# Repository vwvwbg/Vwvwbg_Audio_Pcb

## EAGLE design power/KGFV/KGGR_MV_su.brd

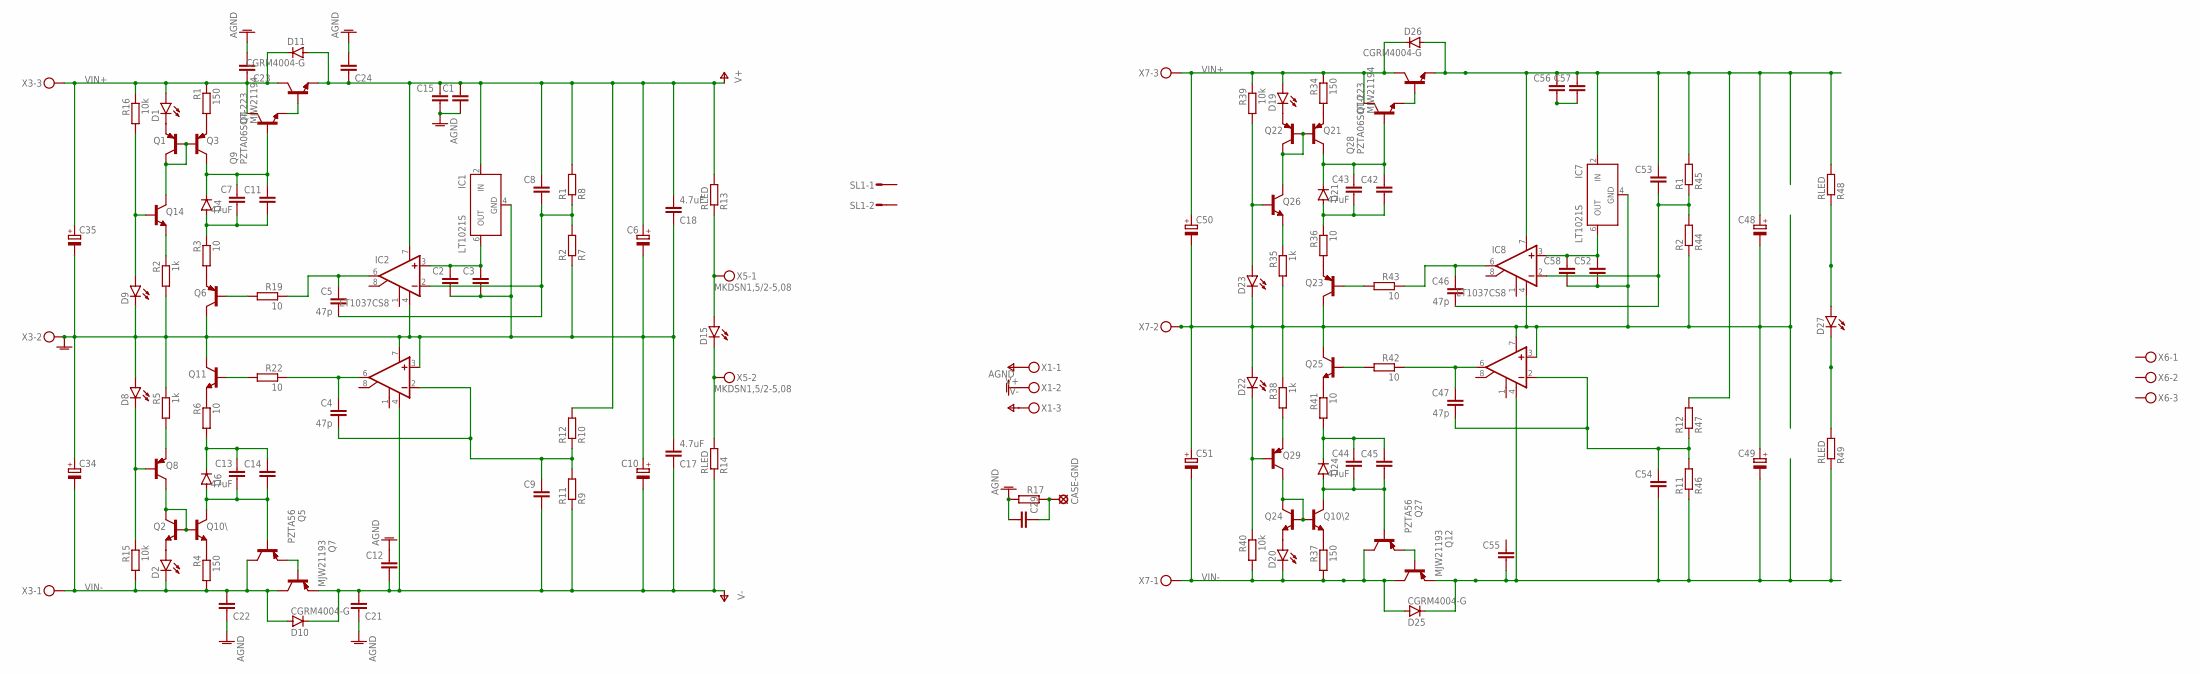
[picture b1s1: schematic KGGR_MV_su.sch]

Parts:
C1, C2, C3, C8, C9, C11, C12, C14, C15, C42, C45, C52, C53, C54, C55, C56, C57, C58: C-EUC0805; C0805
C4, C5, C46, C47: 47p; C0805
C6, C10, C48, C49: CPOL-EUE5-13; E5-13
C7, C13, C43, C44: 47uF; C1206
C17, C18: 4.7uF; C050-075X075
C21, C24: C-EU050-035X075; C050-035X075
C22, C23: C-EU050-075X075; C050-075X075
C29: C-EU102_152-062X184; C102_152-062X184
C34, C35, C50, C51: CPOL-EUE7.5-18; E7,5-18
CASE-GND: SE14
D1, D2, D8, D9, D15, D19, D20, D22, D23, D27: LEDSML0805; SML0805
D4, D21: TZMC10; SOD80C
D6, D24: TZAMC10; SOD80C
D10, D11, D25, D26: CGRM4004-G; SOD-123_MINI-SMA
IC1, IC7: LT1021S; SOIC8
IC2, IC3: LT1037CS8; SOIC8
IC8, IC9: LT1037CS8; SO08
Q1, Q3, Q6, Q8, Q21, Q22, Q23, Q29: TRANSISTOR_BC857C-PNP-SOT23-BEC; TRANSISTOR_SOT23-BEC
Q2, Q10\, Q10\2, Q11, Q14, Q24, Q25, Q26: TRANSISTOR_BC847CLT1-NPN-SOT23-BEC; TRANSISTOR_SOT23-BEC
Q4, Q10: MJW21194; TO-264
Q5, Q27: PZTA56; SOT223
Q7, Q12: MJW21193; TO-264
Q9, Q28: PZTA06SOT-223; SOT223
R1, R4, R34, R37: 150; MINI_MELF-0204W
R2, R5, R35, R38: 1k; MINI_MELF-0204W
R3, R6, R19, R22, R36, R41, R42, R43: 10; MINI_MELF-0204W
R7, R44: R2; MINI_MELF-0204W
R8, R45: R1; MINI_MELF-0204W
R9, R46: R11; MINI_MELF-0204W
R10, R47: R12; MINI_MELF-0204W
R13, R14, R48, R49: RLED; MINI_MELF-0204W
R15, R16, R39, R40: 10k; MINI_MELF-0204W
R17: R-EU_0617/22; 0617/22
SL1: M02S; 02P
X1, X3, X6, X7: MKDSN1,5/3-5,08
X5: MKDSN1,5/2-5,08

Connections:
AGND: C1.2, C2.2, C3.2, C6.-, C10.+, C12.1, C15.2, C17.2, C18.1, C21.1, C22.1, C23.2, C24.2, C29.2, C29.3 (2), C34.+, C35.-, C48.-, C49.+, C50.-, C51.+, C52.2, C55.1, C56.2, C57.2, C58.2, D8.A, D9.C, D22.A, D23.C, IC1.4 (GND), IC2.4 (V-), IC3.3 (+IN), IC3.7 (V+), IC7.4 (GND), IC8.4 (V-), IC9.3 (+IN), IC9.7 (V+), Q6.C, Q11.C, Q23.C, Q25.C, R2.2, R5.1, R7.1, R17.2, R35.2, R38.1, R44.1, X1.2, X3.2, X6.2, X7.2
unnamed: Q1.B, Q1.C, Q3.B, Q14.C
unnamed: D1.C, Q1.E
unnamed: Q3.E, R1.2
unnamed: C7.1, C11.1, D4.C, Q3.C, Q9.1 (B)
unnamed: C7.2, C11.2, D4.A, R3.1
unnamed: Q6.E, R3.2
unnamed: Q14.E, R2.1
unnamed: D9.A, Q14.B, R16.2
unnamed: C4.1, IC3.6 (OUT), R22.1
unnamed: Q8.E, R5.2
unnamed: D8.C, Q8.B, R15.1
unnamed: Q11.E, R6.1
unnamed: C13.1, C14.1, D6.C, R6.2
unnamed: C13.2, C14.2, D6.A, Q5.1 (B), Q10\.C
unnamed: Q2.B, Q2.C, Q8.C, Q10\.B
unnamed: Q5.3 (E), Q7.B
unnamed: Q10\.E, R4.1
unnamed: D2.A, Q2.E
unnamed: Q4.B, Q9.3 (E)
unnamed: C4.2, C9.1, IC3.2 (-IN), R9.2, R10.1
unnamed: C5.1, IC2.6 (OUT), R19.1
unnamed: Q11.B, R22.2
unnamed: Q6.B, R19.2
unnamed: C5.2, C8.2, IC2.2 (-IN), R7.2, R8.1
unnamed: C2.1, C3.1, IC1.6 (OUT), IC2.3 (+IN)
unnamed: D15.C, R14.2, X5.2
unnamed: D15.A, R13.1, X5.1
unnamed: C29.1, CASE-GND.MP, R17.1
unnamed: Q21.B, Q22.B, Q22.C, Q26.C
unnamed: D19.C, Q22.E
unnamed: Q21.E, R34.2
unnamed: C42.1, C43.1, D21.C, Q21.C, Q28.1 (B)
unnamed: C42.2, C43.2, D21.A, R36.1
unnamed: Q23.E, R36.2
unnamed: Q26.E, R35.1
unnamed: D23.A, Q26.B, R39.2
unnamed: Q29.E, R38.2
unnamed: D22.C, Q29.B, R40.1
unnamed: Q25.E, R41.1
unnamed: C44.1, C45.1, D24.C, R41.2
unnamed: C44.2, C45.2, D24.A, Q10\2.C, Q27.1 (B)
unnamed: Q10\2.B, Q24.B, Q24.C, Q29.C
unnamed: Q10\2.E, R37.1
unnamed: D20.A, Q24.E
unnamed: Q12.B, Q27.3 (E)
unnamed: Q10.B, Q28.3 (E)
unnamed: Q25.B, R42.2
unnamed: Q23.B, R43.2
unnamed: C46.2, C53.2, IC8.2 (-IN), R44.2, R45.1
unnamed: D27.C, R49.2
unnamed: D27.A, R48.1
unnamed: C47.1, IC9.6 (OUT), R42.1
unnamed: C47.2, C54.1, IC9.2 (-IN), R46.2, R47.1
unnamed: C52.1, C58.1, IC7.6 (OUT), IC8.3 (+IN)
unnamed: C46.1, IC8.6 (OUT), R43.1
V+: C1.1, C6.+, C8.1, C15.1, C18.2, C24.1, D11.A, IC1.2 (IN), IC2.7 (V+), Q4.E, R8.2, R10.2, R13.2, X1.1
V+2: C48.+, C53.1, C56.1, C57.1, D26.A, IC7.2 (IN), IC8.7 (V+), Q10.E, R45.2, R47.2, R48.2, X6.1
V-: C9.2, C10.-, C12.2, C17.1, C21.2, D10.C, IC3.4 (V-), Q7.E, R9.1, R14.1, X1.3
V-2: C49.-, C54.2, C55.2, D25.C, IC9.4 (V-), Q12.E, R46.1, R49.1, X6.3
VIN+: C23.1, C35.+, C50.+, D1.A, D11.C, D19.A, D26.C, Q4.C, Q9.2 (C), Q9.4 (C), Q10.C, Q28.2 (C), Q28.4 (C), R1.1, R16.1, R34.1, R39.1, X3.3, X7.3
VIN-: C22.2, C34.-, C51.-, D2.C, D10.A, D20.C, D25.A, Q5.2 (C), Q5.4 (C), Q7.C, Q12.C, Q27.2 (C), Q27.4 (C), R4.2, R15.2, R37.2, R40.2, X3.1, X7.1

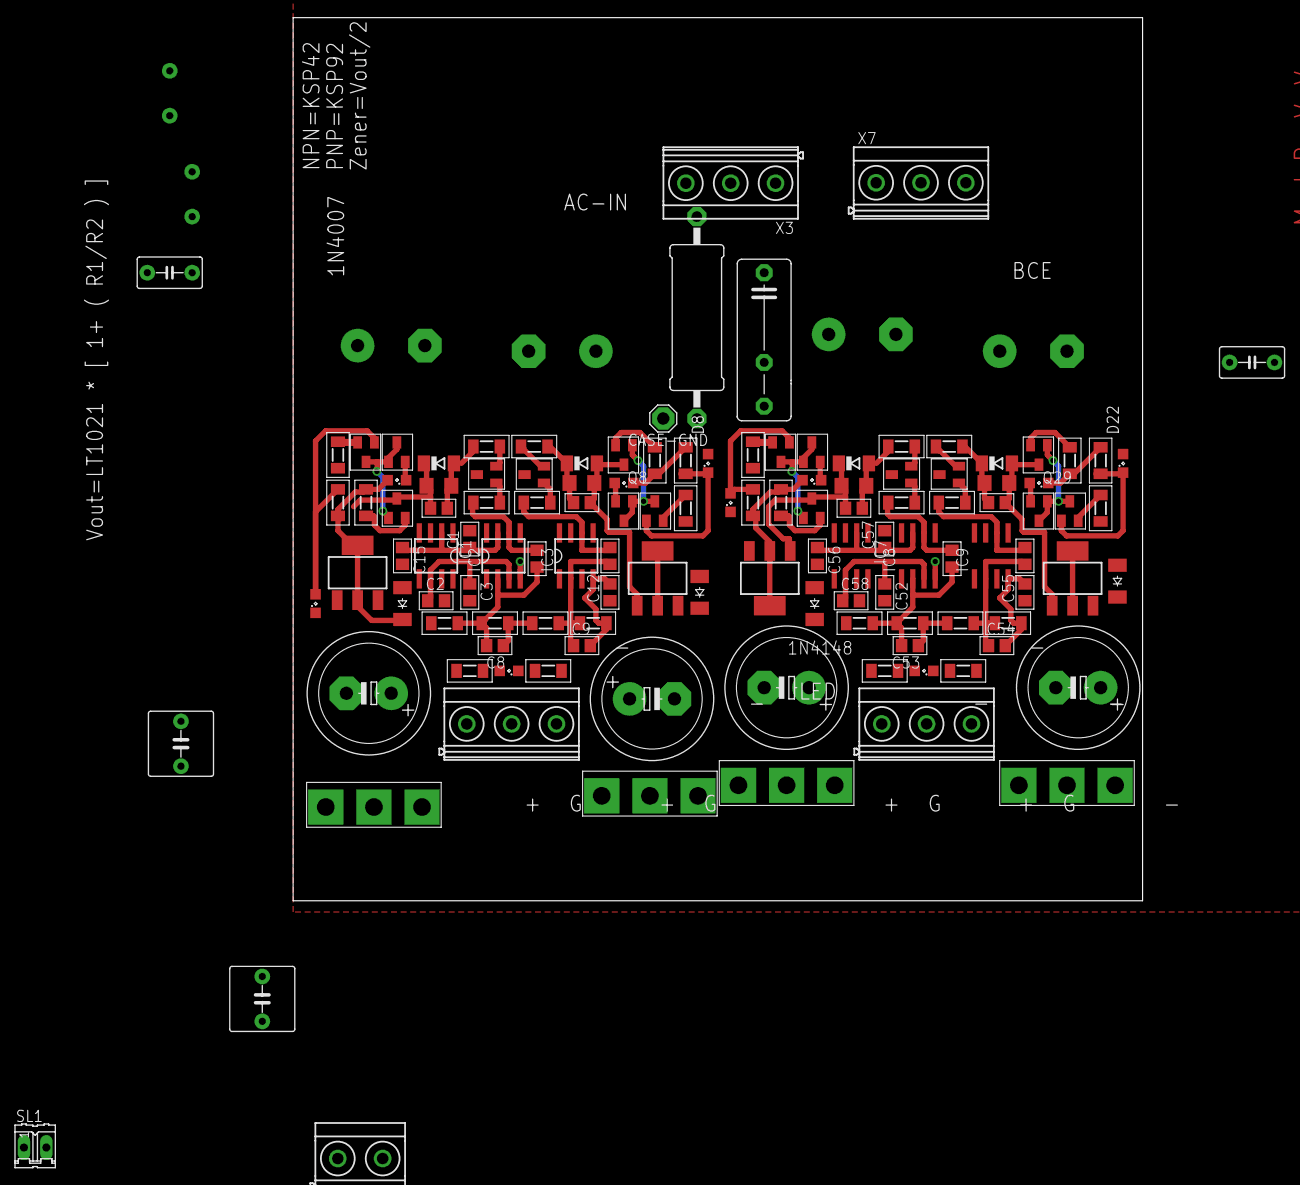
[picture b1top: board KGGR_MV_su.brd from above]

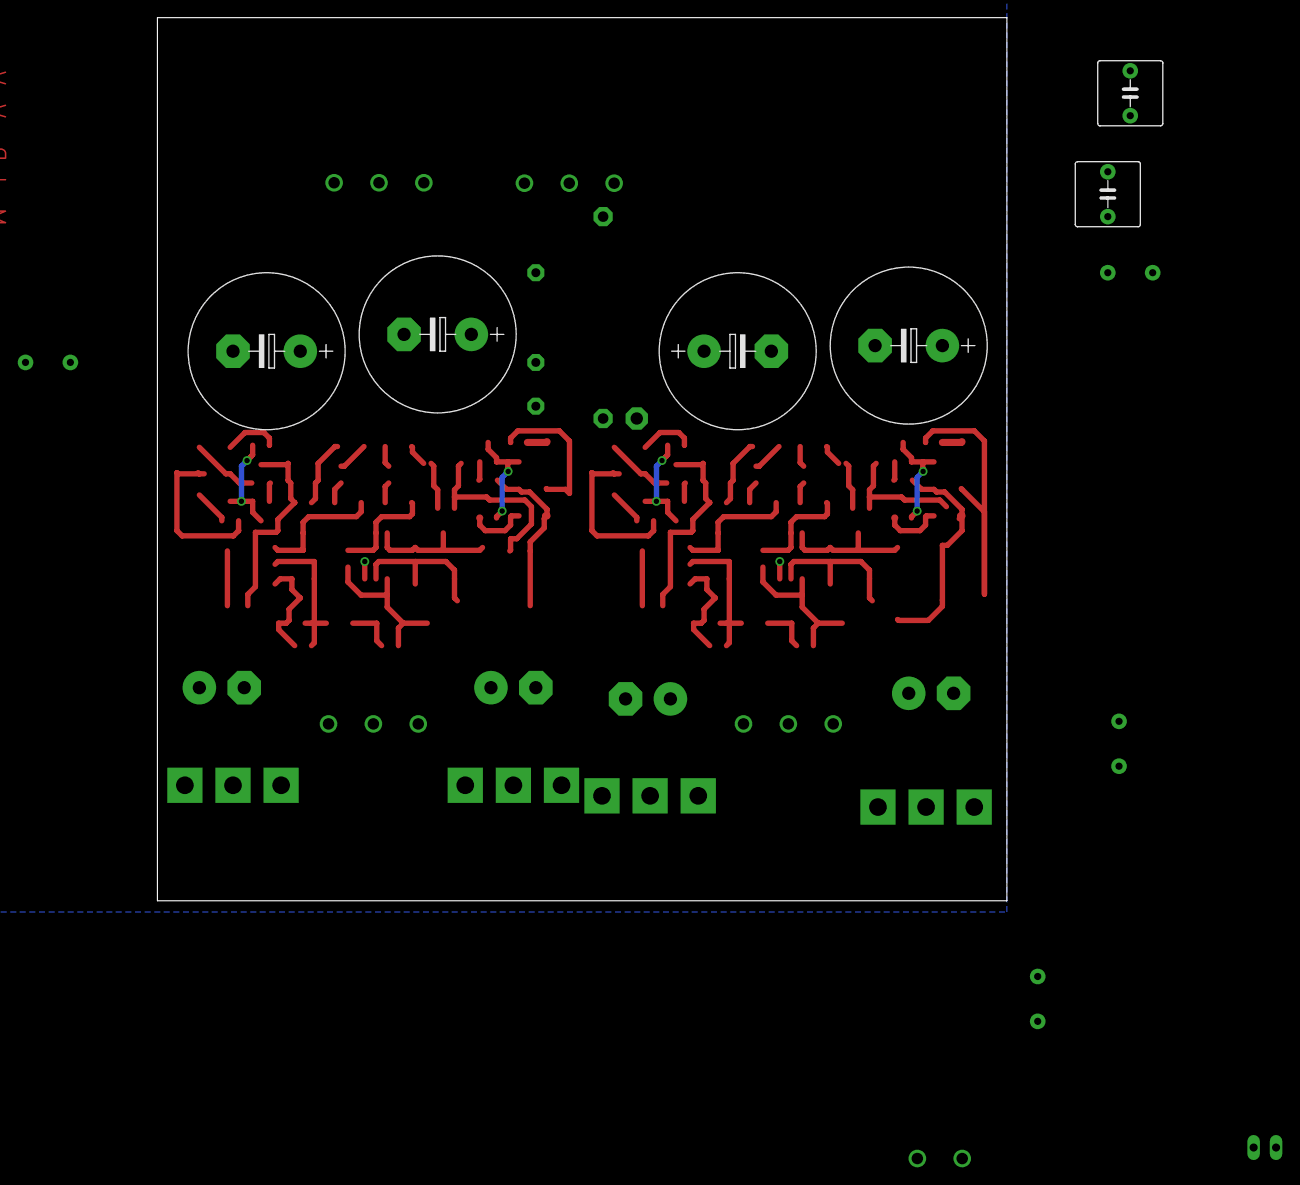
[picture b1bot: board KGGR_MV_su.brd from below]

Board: 2 copper layers, 96.2 x 100.0 mm, 129 parts (6 on the bottom side), 62 nets.

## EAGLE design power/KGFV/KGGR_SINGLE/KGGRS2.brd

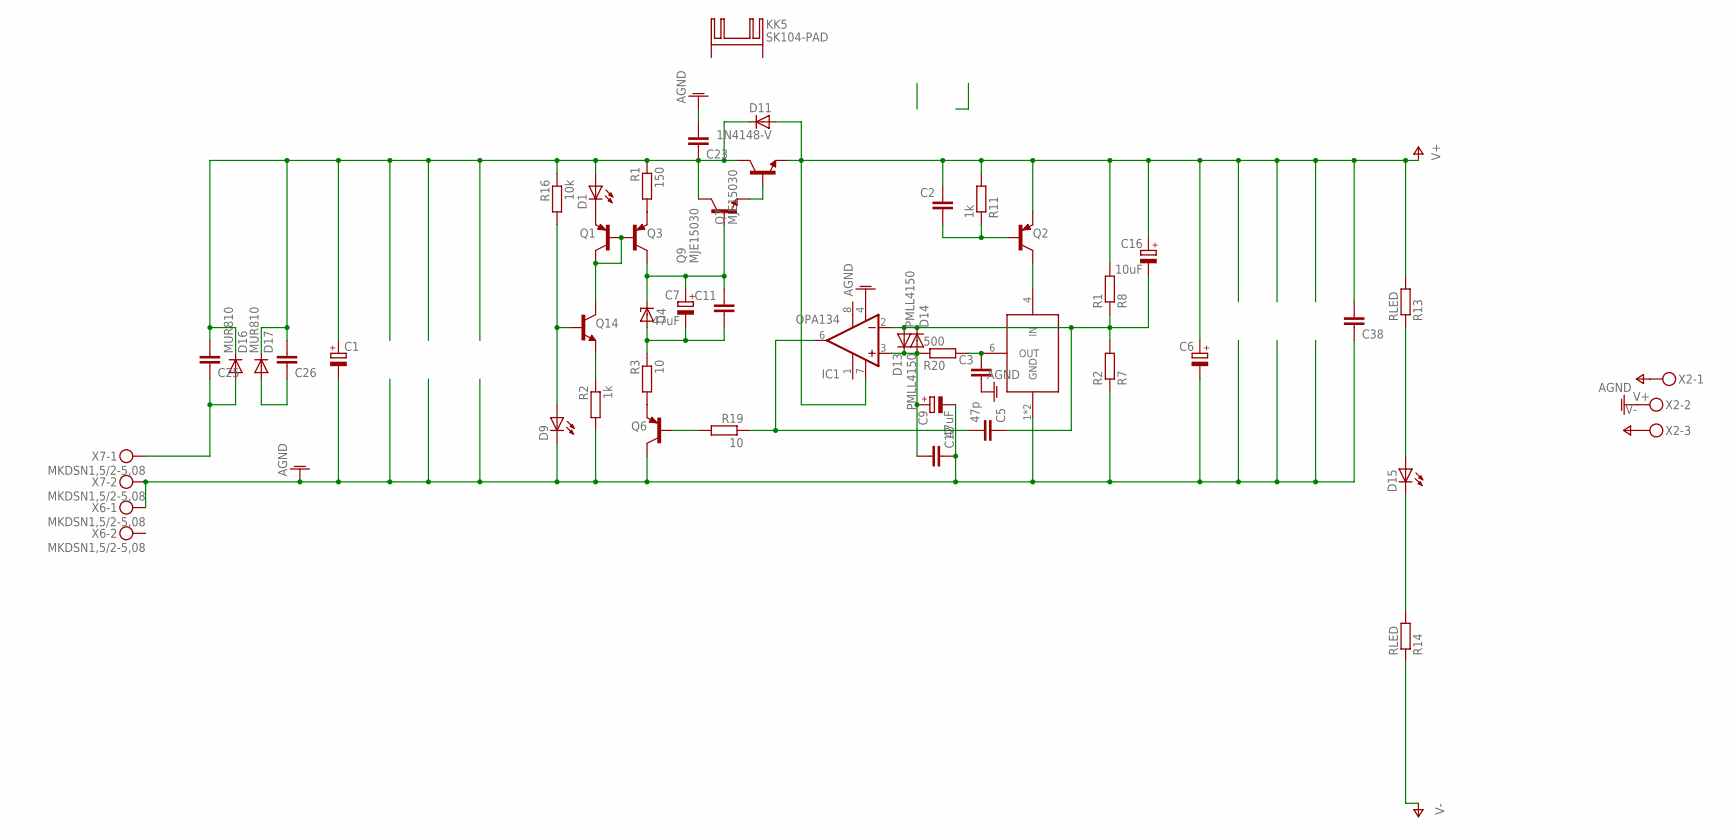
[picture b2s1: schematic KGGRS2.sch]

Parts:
C1: CPOL-EUE10-35; EB35D
C2, C3, C11: C-EUC1206; C1206
C5: 47p; C1206
C6: CPOL-EUE5-13; E5-13
C7, C9: 47uF; SP-CAP-CX
C12, C25, C26, C38: C-EU050-035X075; C050-035X075
C16: 10uF; SP-CAP-CX
C23: C-EU050-075X075; C050-075X075
D1, D9, D15: LED5MM
D4: ZENER-DIODESOD80C; SOD80C
D11: 1N4148-V; 1N4148
D13, D14: PMLL4150; SOD80C
D16, D17: MUR810; TO220ACS
IC1: OPA134; SO08
KK5: SK104-PAD
Q1, Q2, Q3, Q6: MMBTA92LT1-PNP-SOT23-BEC; SOT23-BEC
Q7, Q9: MJE15030; TO220KG
Q14: MMBTA42LT1-NPN-SOT23-BEC; SOT23-BEC
R1: 150; MINI_MELF-0204W
R2, R11: 1k; MINI_MELF-0204W
R3, R19: 10; MINI_MELF-0204W
R7: R2; MINI_MELF-0204W
R8: R1; MINI_MELF-0204W
R13: RLED; MINI_MELF-0204W
R14: RLED; 0207/2V
R16: 10k; MINI_MELF-0204W
R20: 500; MINI_MELF-0204W
U$1: LTC6654; SOT-23-6
X2: MKDSN1,5/3-5,08
X6, X7: MKDSN1,5/2-5,08

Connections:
AGND: C1.-, C3.2, C6.-, C9.-, C12.1, C23.2, C38.1, D9.K (C), IC1.4 (V-), Q6.C, R2.2, R7.1, U$1.1 (GND), U$1.2 (GND), X2.2, X6.1, X7.2
unnamed: Q1.B, Q1.C, Q3.B, Q14.C
unnamed: D1.K (C), Q1.E
unnamed: Q3.E, R1.2
unnamed: C1.+, C23.1, C25.2, C26.2, D1.A, D11.C, D16.C, D17.C, Q7.2 (C), Q9.2 (C), R1.1, R16.1
unnamed: C7.+, C11.1, D4.C, Q3.C, Q9.1 (B)
unnamed: C7.-, C11.2, D4.A, R3.1
unnamed: Q6.E, R3.2
unnamed: Q14.E, R2.1
unnamed: D9.A, Q14.B, R16.2
unnamed: C3.1, R20.2, U$1.6 (OUT)
unnamed: C2.2, Q2.B, R11.1
unnamed: Q2.C, U$1.4 (IN)
unnamed: Q7.1 (B), Q9.3 (E)
unnamed: C25.1, D16.A, X7.1
unnamed: C5.2, IC1.6 (OUT), R19.1
unnamed: Q6.B, R19.2
unnamed: C5.1, C16.-, D13.A, D14.C, IC1.2 (-IN), R7.2, R8.1
unnamed: C9.+, C12.2, D13.C, D14.A, IC1.3 (+IN), R20.1
unnamed: D15.K (C), R14.2
unnamed: D15.A, R13.1
unnamed: C26.1, D17.A
V+: C2.1, C6.+, C16.+, C38.2, D11.A, IC1.7 (V+), Q2.E, Q7.3 (E), R8.2, R11.2, R13.2, X2.1
V-: R14.1, X2.3

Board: 2 copper layers, 47 parts (12 on the bottom side), 24 nets, no tracks yet.

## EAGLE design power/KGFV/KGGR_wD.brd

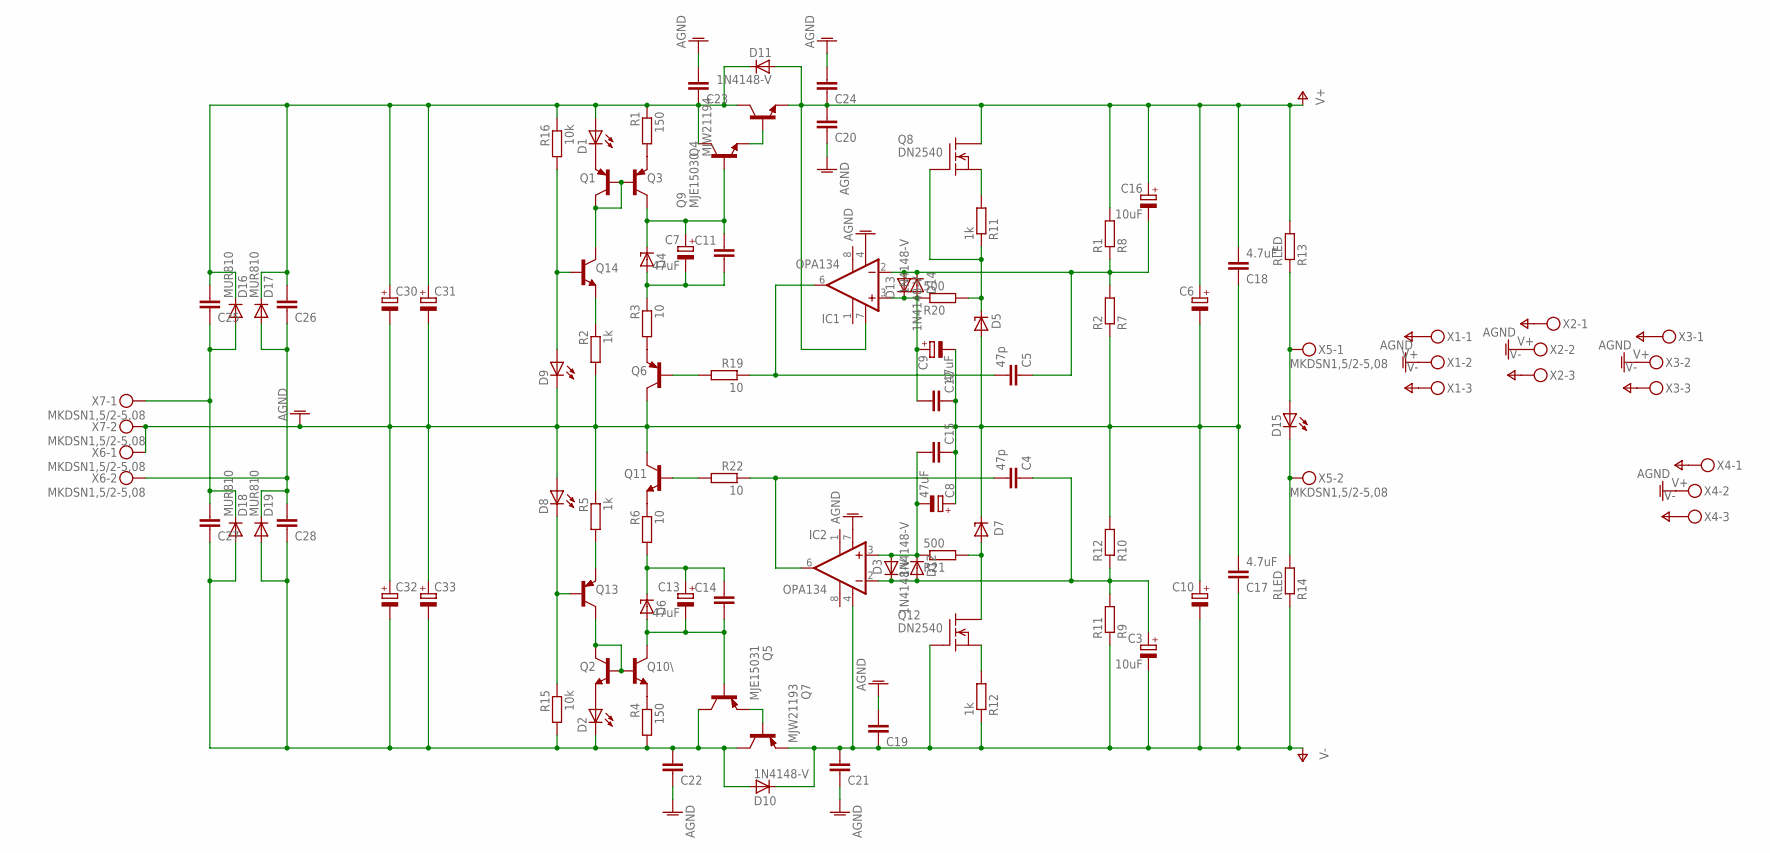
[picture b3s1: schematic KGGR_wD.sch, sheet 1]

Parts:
C3, C16: 10uF; E5-8,5
C4, C5: 47p; C025_050-025X075
C6, C10, C30, C31, C32, C33: CPOL-EUE7.5-18; E7,5-18
C7, C8, C9, C13: 47uF; E5-8,5
C11, C12, C14, C15, C19, C20, C21, C24, C25, C26, C27, C28: C-EU050-035X075; C050-035X075
C17, C18: 4.7uF; C050-075X075
C22, C23: C-EU050-075X075; C050-075X075
D1, D2, D8, D9, D15: LED5MM
D3, D10, D11, D12, D13, D14: 1N4148-V; 1N4148
D4, D6: 1N4728; DO41Z10
D5, D7: LT1021; DIL08
D16, D17, D18, D19: MUR810; TO220ACS
IC1, IC2: OPA134; DIL08
Q1, Q3, Q6, Q13: MPSA92-PNP-TO92-EBC; TO92-EBC
Q2, Q10\, Q11, Q14: MPSA42-NPN-TO92-EBC; TO92-EBC
Q4: MJW21194; TO-264
Q5: MJE15031; TO220KG
Q7: MJW21193; TO-264
Q8, Q12: DN2540; TO92-
Q9: MJE15030; TO220KG
R1, R4: 150; 0309/12
R2, R5, R11, R12: 1k; 0309/12
R3, R6, R19, R22: 10; 0309/12
R7: R2; 0309/12
R8: R1; 0309/12
R9: R11; 0309/12
R10: R12; 0309/12
R13, R14: RLED; 0309/12
R15, R16: 10k; 0309/12
R20, R21: 500; 0309/12
X1, X2, X3, X4: MKDSN1,5/3-5,08
X5, X6, X7: MKDSN1,5/2-5,08

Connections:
AGND: C6.-, C8.+, C9.-, C10.+, C12.1, C15.1, C17.2, C18.1, C19.2, C20.1, C21.1, C22.1, C23.2, C24.2, C30.-, C31.-, C32.+, C33.+, D5.4 (GND), D7.6 (OUT), D8.A, D9.K (C), IC1.4 (V-), IC2.7 (V+), Q6.C, Q11.C, R2.2, R5.1, R7.1, R10.2, X1.2, X2.2, X3.2, X4.2, X6.1, X7.2
unnamed: Q1.B, Q1.C, Q3.B, Q14.C
unnamed: D1.K (C), Q1.E
unnamed: Q3.E, R1.2
unnamed: C23.1, C25.2, C26.2, C30.+, C31.+, D1.A, D11.C, D16.C, D17.C, Q4.C, Q9.2 (C), R1.1, R16.1
unnamed: C7.+, C11.1, D4.C, Q3.C, Q9.1 (B)
unnamed: C7.-, C11.2, D4.A, R3.1
unnamed: Q6.E, R3.2
unnamed: Q14.E, R2.1
unnamed: D9.A, Q14.B, R16.2
unnamed: C8.-, C15.2, D3.A, D12.C, IC2.3 (+IN), R21.1
unnamed: Q13.E, R5.2
unnamed: D8.K (C), Q13.B, R15.1
unnamed: Q11.E, R6.1
unnamed: C13.+, C14.1, D6.C, R6.2
unnamed: C13.-, C14.2, D6.A, Q5.1 (B), Q10\.C
unnamed: Q2.B, Q2.C, Q10\.B, Q13.C
unnamed: Q5.3 (E), Q7.B
unnamed: Q10\.E, R4.1
unnamed: D2.A, Q2.E
unnamed: Q4.B, Q9.3 (E)
unnamed: C22.2, C27.1, C28.1, C32.-, C33.-, D2.K (C), D10.A, D18.A, D19.A, Q5.2 (C), Q7.C, R4.2, R15.2
unnamed: C25.1, C27.2, D16.A, D18.C, X7.1
unnamed: C5.2, C5.3 (2), IC1.6 (OUT), R19.1
unnamed: C4.2, C4.3 (2), IC2.6 (OUT), R22.1
unnamed: Q11.B, R22.2
unnamed: Q6.B, R19.2
unnamed: C5.1, C16.-, D13.A, D14.C, IC1.2 (-IN), R7.2, R8.1
unnamed: Q12.3 (S), R12.2
unnamed: D5.6 (OUT), Q8.2 (G), R11.1, R20.2
unnamed: C9.+, C12.2, D13.C, D14.A, IC1.3 (+IN), R20.1
unnamed: D15.K (C), R14.2, X5.2
unnamed: D7.4 (GND), Q12.1 (D), R21.2
unnamed: C3.+, C4.1, D3.C, D12.A, IC2.2 (-IN), R9.2, R10.1
unnamed: Q8.3 (S), R11.2
unnamed: D15.A, R13.1, X5.1
unnamed: C26.1, C28.2, D17.A, D19.C, X6.2
V+: C6.+, C16.+, C18.2, C20.2, C24.1, D11.A, IC1.7 (V+), Q4.E, Q8.1 (D), R8.2, R13.2, X1.1, X2.1, X3.1, X4.1
V-: C3.-, C10.-, C17.1, C19.1, C21.2, D10.C, IC2.4 (V-), Q7.E, Q12.2 (G), R9.1, R12.1, R14.1, X1.3, X2.3, X3.3, X4.3

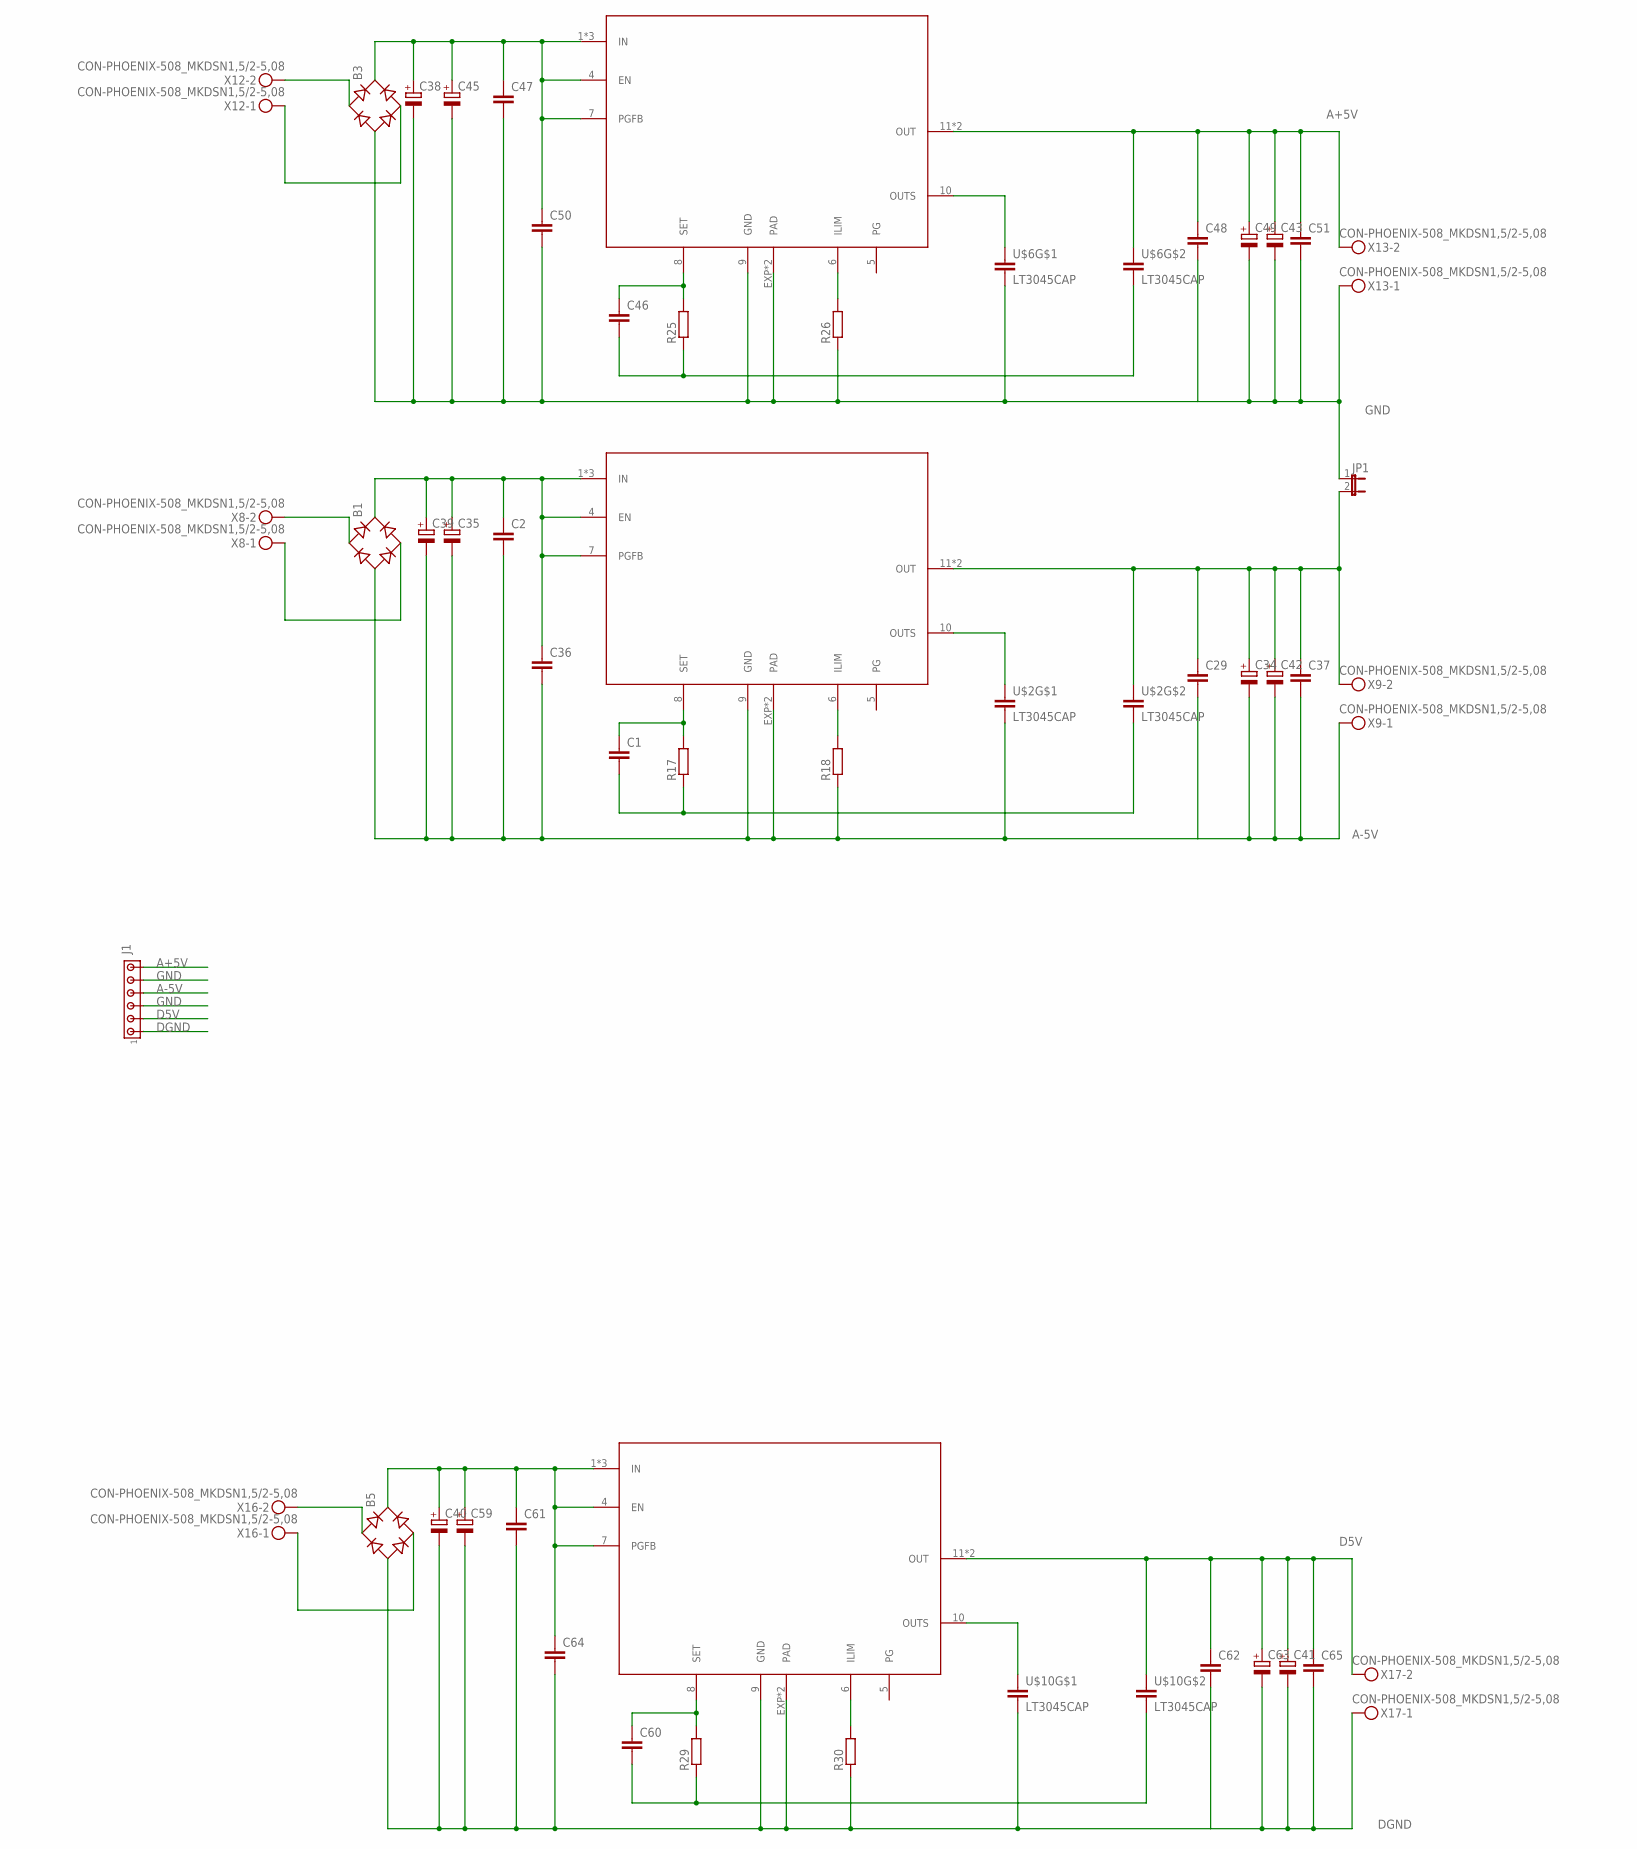
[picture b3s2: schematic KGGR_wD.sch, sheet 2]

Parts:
B1, B3, B5: RB1A
C1, C36, C37, C46, C50, C51, C60, C64, C65: C-EUC1206; C1206
C2, C29, C47, C48, C61, C62: C-EU050-050X075; C050-050X075
C34, C49, C63: CPOL-EUE5-10.5; E5-10,5
C35, C45, C59: CPOL-EUE7.5-18; E7,5-18
C38, C39, C40, C41, C42, C43: CPOL-EUSP-CAP-CX; SP-CAP-CX
J1: MTA06-156; 1X6MTA
JP1: JP1E; JP1
R17, R18, R25, R26, R29, R30: R-EU_MELF0204R; MINI_MELF-0204R
U$1, U$5, U$9: LT3045; MSOP12
U$2, U$6, U$10: LT3045CAP
X8, X9, X12, X13, X16, X17: CON-PHOENIX-508_MKDSN1,5/2-5,08

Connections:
A+5V: C43.+, C48.1, C49.+, C51.1, J1.6, U$5.11 (OUT), U$5.12 (OUT), U$6.4 (1), X13.2
A-5V: B1.-, C2.2, C29.2, C34.-, C35.-, C36.2, C37.2, C39.-, C42.-, J1.4, R18.1, U$1.9 (GND), U$1.EXP (PAD), U$1.EXP1 (PAD), U$2.5 (2), X9.1
D5V: C41.+, C62.1, C63.+, C65.1, J1.2, U$9.11 (OUT), U$9.12 (OUT), U$10.4 (1), X17.2
DGND: B5.-, C40.-, C41.-, C59.-, C61.2, C62.2, C63.-, C64.2, C65.2, J1.1, R30.1, U$9.9 (GND), U$9.EXP (PAD), U$9.EXP1 (PAD), U$10.5 (2), X17.1
GND: B3.-, C38.-, C43.-, C45.-, C47.2, C48.2, C49.-, C50.2, C51.2, J1.3, J1.5, JP1.1, R26.1, U$5.9 (GND), U$5.EXP (PAD), U$5.EXP1 (PAD), U$6.5 (2), X13.1
IN1: B1.+, C2.1, C35.+, C36.1, C39.+, U$1.1 (IN), U$1.2 (IN), U$1.3 (IN), U$1.4 (EN), U$1.7 (PGFB)
IN2: B3.+, C38.+, C45.+, C47.1, C50.1, U$5.1 (IN), U$5.2 (IN), U$5.3 (IN), U$5.4 (EN), U$5.7 (PGFB)
IN3: B5.+, C40.+, C59.+, C61.1, C64.1, U$9.1 (IN), U$9.2 (IN), U$9.3 (IN), U$9.4 (EN), U$9.7 (PGFB)
unnamed: U$1.10 (OUTS), U$2.3 (1)
unnamed: U$5.10 (OUTS), U$6.3 (1)
unnamed: R18.2, U$1.6 (ILIM)
unnamed: B1.AC2, X8.1
unnamed: B1.AC1, X8.2
unnamed: R26.2, U$5.6 (ILIM)
unnamed: B3.AC2, X12.1
unnamed: B3.AC1, X12.2
unnamed: U$9.10 (OUTS), U$10.3 (1)
unnamed: R30.2, U$9.6 (ILIM)
unnamed: B5.AC2, X16.1
unnamed: B5.AC1, X16.2
OUT1: C29.1, C34.+, C37.1, C42.+, JP1.2, U$1.11 (OUT), U$1.12 (OUT), U$2.4 (1), X9.2
SET1: C1.1, R17.2, U$1.8 (SET)
SET2: C46.1, R25.2, U$5.8 (SET)
SET3: C60.1, R29.2, U$9.8 (SET)
SGND1: C1.2, R17.1, U$2.6 (2)
SGND2: C46.2, R25.1, U$6.6 (2)
SGND3: C60.2, R29.1, U$10.6 (2)

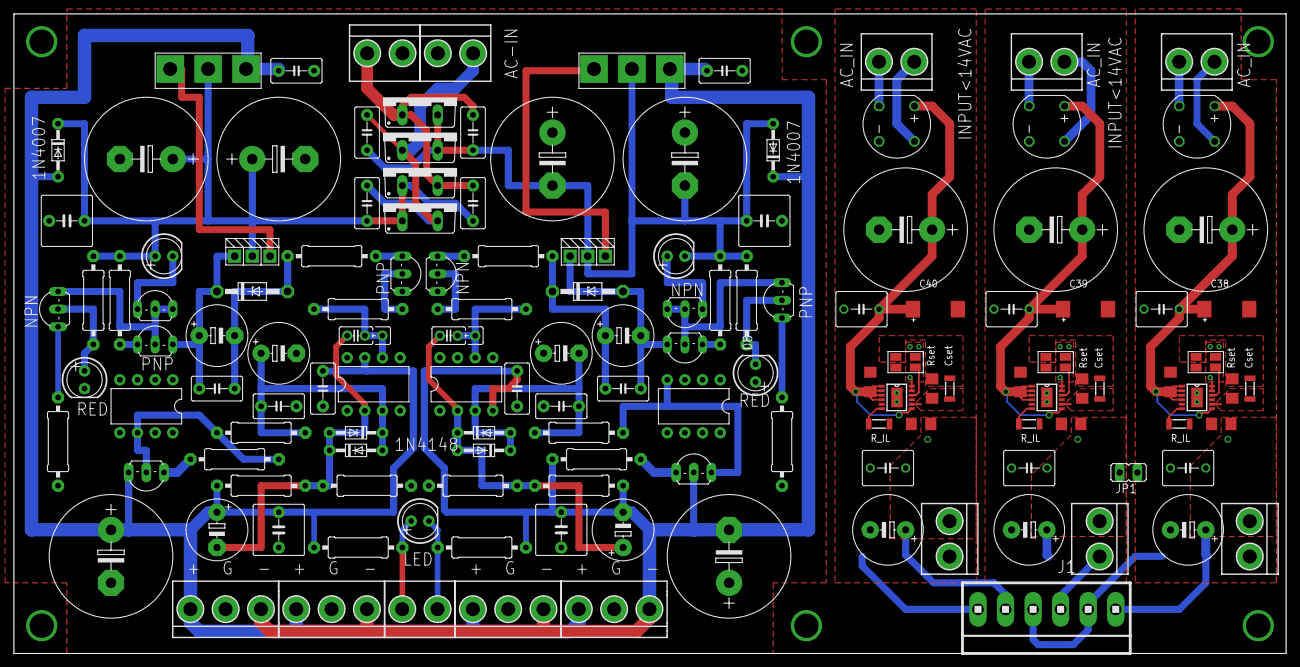
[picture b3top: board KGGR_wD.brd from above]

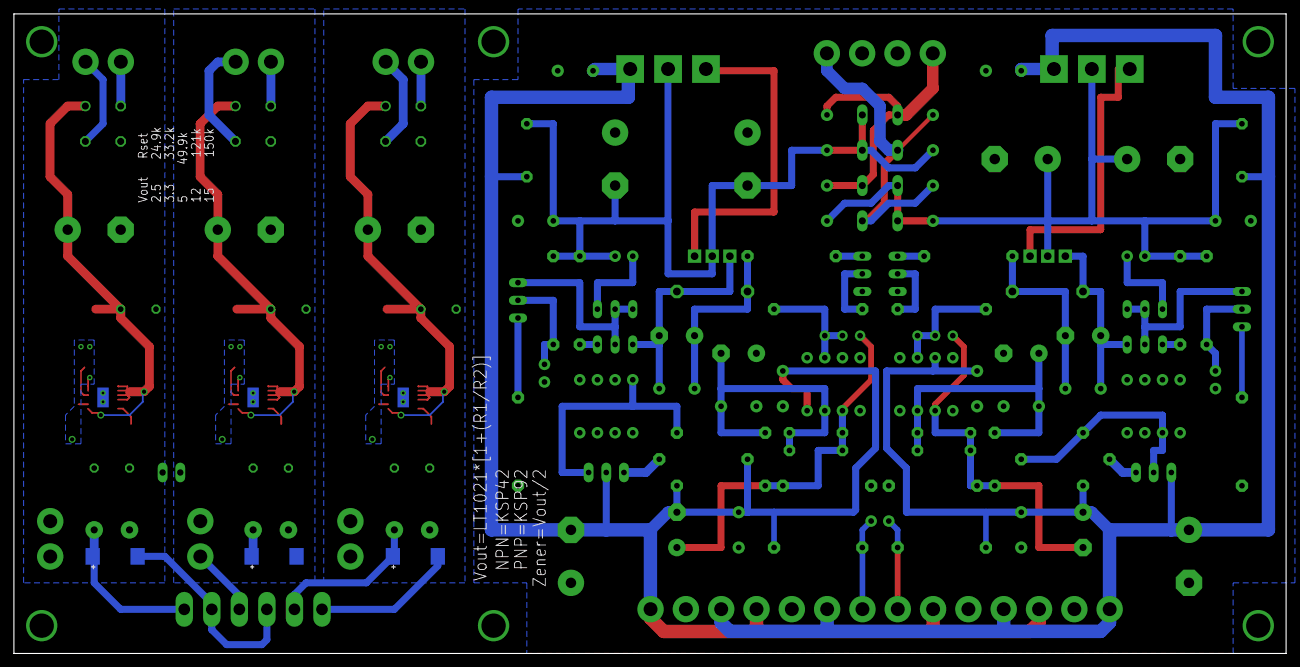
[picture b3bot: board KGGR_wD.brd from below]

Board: 2 copper layers, 183.0 x 92.0 mm, 142 parts (3 on the bottom side), 66 nets.

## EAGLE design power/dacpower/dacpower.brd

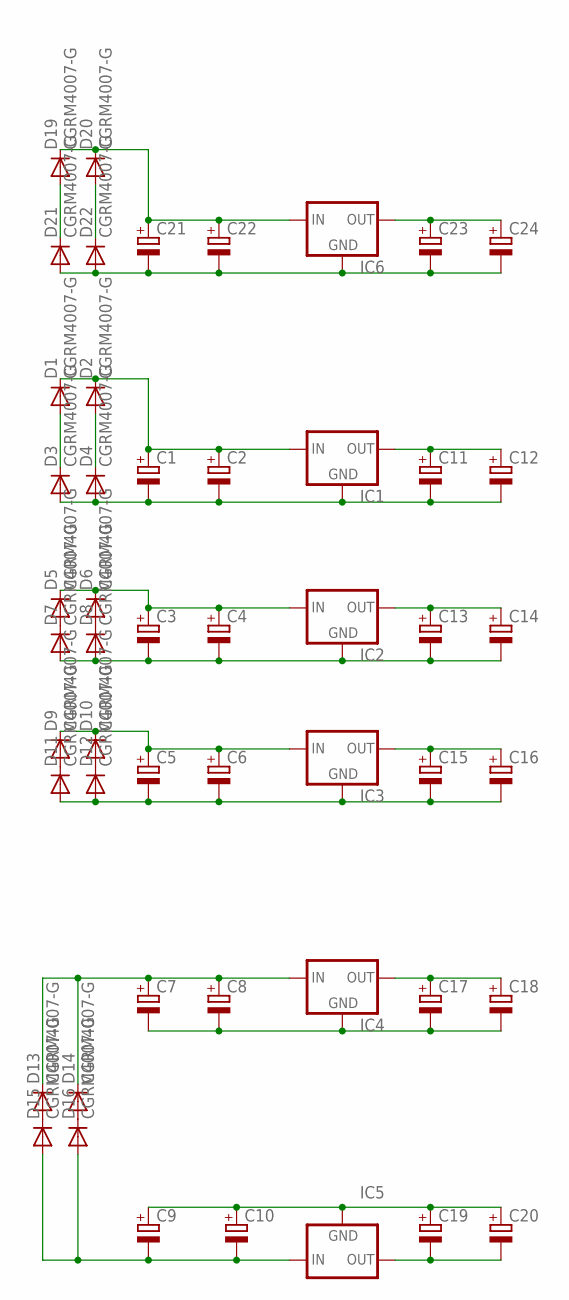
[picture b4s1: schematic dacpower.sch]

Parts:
C1, C2, C3, C4, C5, C6, C7, C8, C9, C10, C21, C22: CPOL-EUE7.5-18; E7,5-18
C11, C12, C13, C14, C15, C16, C17, C18, C19, C20, C23, C24: CPOL-EUSP-CAP-CX; SP-CAP-CX
D1, D2, D3, D4, D5, D6, D7, D8, D9, D10, D11, D12, D13, D14, D15, D16, D19, D20, D21, D22: CGRM4007-G; SOD-123_MINI-SMA
IC1, IC2, IC3, IC4, IC6: 78XXS
IC5: 79XXS

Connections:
unnamed: C1.+, C2.+, D1.C, D2.C, IC1.IN
unnamed: C1.-, C2.-, C11.-, C12.-, D3.A, D4.A, IC1.GND
unnamed: C3.+, C4.+, D5.C, D6.C, IC2.IN
unnamed: C3.-, C4.-, C13.-, C14.-, D7.A, D8.A, IC2.GND
unnamed: C5.+, C6.+, D9.C, D10.C, IC3.IN
unnamed: C5.-, C6.-, C15.-, C16.-, D11.A, D12.A, IC3.GND
unnamed: C7.+, C8.+, D13.C, D14.C, IC4.IN
unnamed: C7.-, C8.-, C17.-, C18.-, IC4.GND
unnamed: C9.+, C10.+, C19.+, C20.+, IC5.GND
unnamed: C9.-, C10.-, D15.A, D16.A, IC5.IN
unnamed: C19.-, C20.-, IC5.OUT
unnamed: D1.A, D3.C
unnamed: C17.+, C18.+, IC4.OUT
unnamed: C15.+, C16.+, IC3.OUT
unnamed: C13.+, C14.+, IC2.OUT
unnamed: C11.+, C12.+, IC1.OUT
unnamed: D5.A, D7.C
unnamed: D6.A, D8.C
unnamed: D9.A, D11.C
unnamed: D10.A, D12.C
unnamed: D13.A, D15.C
unnamed: D14.A, D16.C
unnamed: D2.A, D4.C
unnamed: C21.+, C22.+, D19.C, D20.C, IC6.IN
unnamed: C21.-, C22.-, C23.-, C24.-, D21.A, D22.A, IC6.GND
unnamed: C23.+, C24.+, IC6.OUT
unnamed: D19.A, D21.C
unnamed: D20.A, D22.C

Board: 2 copper layers, 50 parts (0 on the bottom side), 28 nets, no tracks yet.

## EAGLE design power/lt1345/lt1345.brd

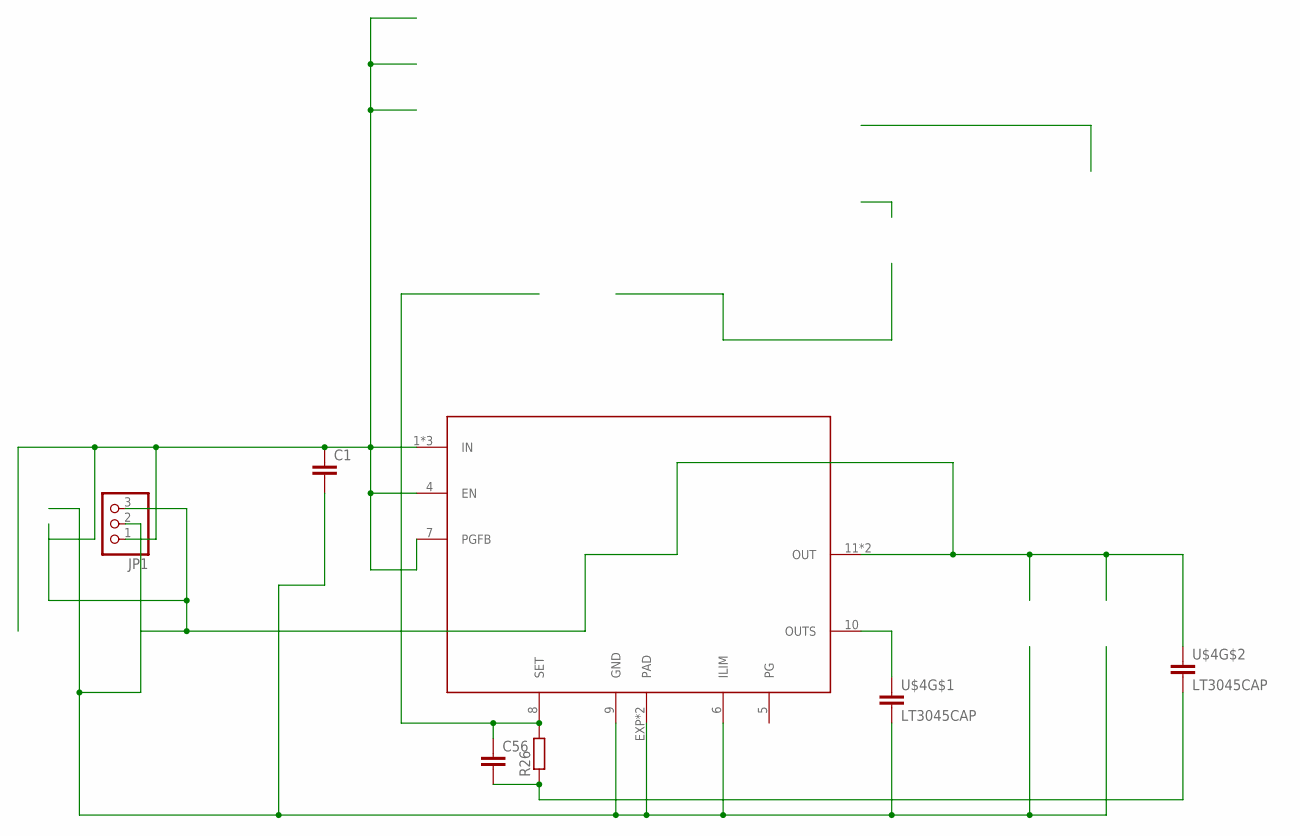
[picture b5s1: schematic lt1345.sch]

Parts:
C1: C-EUC1206; C1206
C56: C-EUC0805; C0805
JP1: PINHD-1X3; 1X03
R26: R-EU_MELF0204R; MINI_MELF-0204R
U$2: LT3045; MSOP12
U$4: LT3045CAP

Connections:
GND: C1.2, JP1.2, U$2.6 (ILIM), U$2.9 (GND), U$2.EXP (PAD), U$2.EXP1 (PAD), U$4.5 (2)
unnamed: C56.1, R26.2, U$2.8 (SET)
unnamed: U$2.10 (OUTS), U$4.3 (1)
unnamed: C56.2, R26.1, U$4.6 (2)
VIN: C1.1, JP1.1, U$2.1 (IN), U$2.2 (IN), U$2.3 (IN), U$2.4 (EN), U$2.7 (PGFB)
VOUT: JP1.3, U$2.11 (OUT), U$2.12 (OUT), U$4.4 (1)

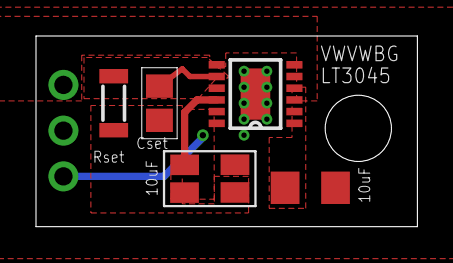
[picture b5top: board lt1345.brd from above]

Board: 2 copper layers, 21.2 x 10.6 mm, 6 parts (0 on the bottom side), 6 nets.
